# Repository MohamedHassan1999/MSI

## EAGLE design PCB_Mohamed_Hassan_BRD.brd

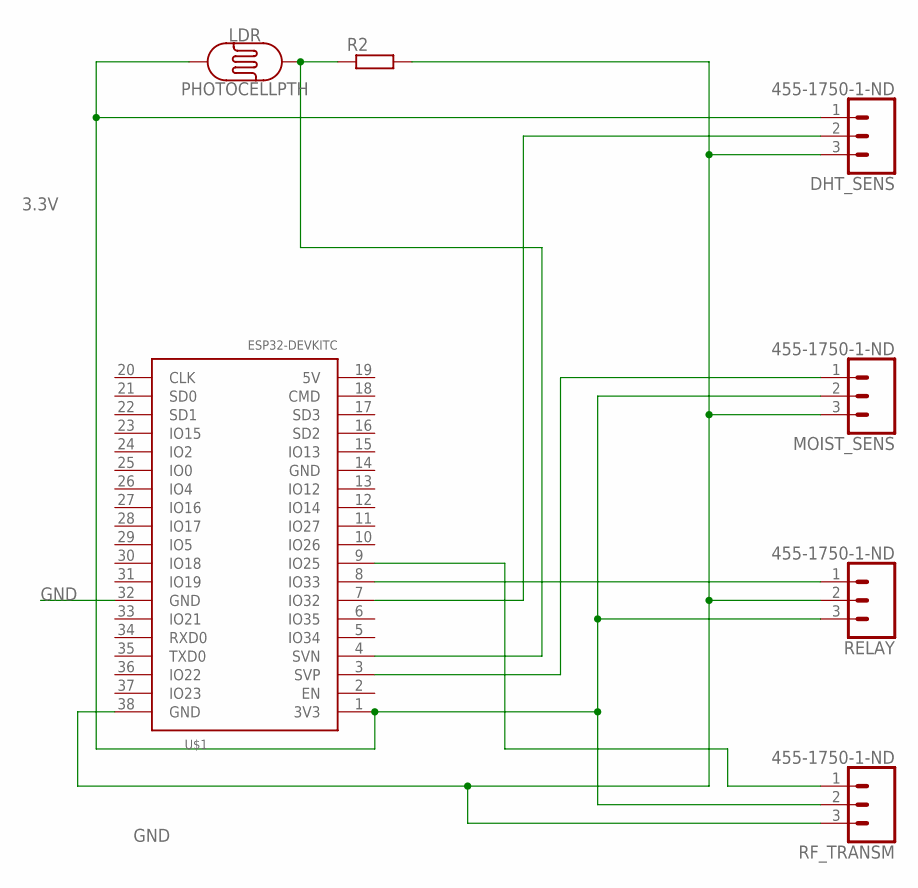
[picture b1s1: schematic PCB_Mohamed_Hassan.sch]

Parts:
DHT_SENS: 455-1750-1-ND; 1X03
LDR: PHOTOCELLPTH; PHOTOCELL
MOIST_SENS: 455-1750-1-ND; 1X03
R2: R-EU_0207/10; 0207/10
RELAY: 455-1750-1-ND; 1X03
RF_TRANSM: 455-1750-1-ND; 1X03
U$1: ESP32DEVKITC; ESP32-DEVKITC

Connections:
3.3V: DHT_SENS.1, LDR.1, MOIST_SENS.2, RELAY.3, RF_TRANSM.2, U$1.1 (3V3)
GND: DHT_SENS.3, MOIST_SENS.3, R2.2, RELAY.2, RF_TRANSM.3, U$1.32 (GND), U$1.38 (GND)
unnamed: LDR.2, R2.1, U$1.4 (SVN)
unnamed: DHT_SENS.2, U$1.7 (IO32)
unnamed: RELAY.1, U$1.8 (IO33)
unnamed: MOIST_SENS.1, U$1.3 (SVP)
unnamed: RF_TRANSM.1, U$1.9 (IO25)

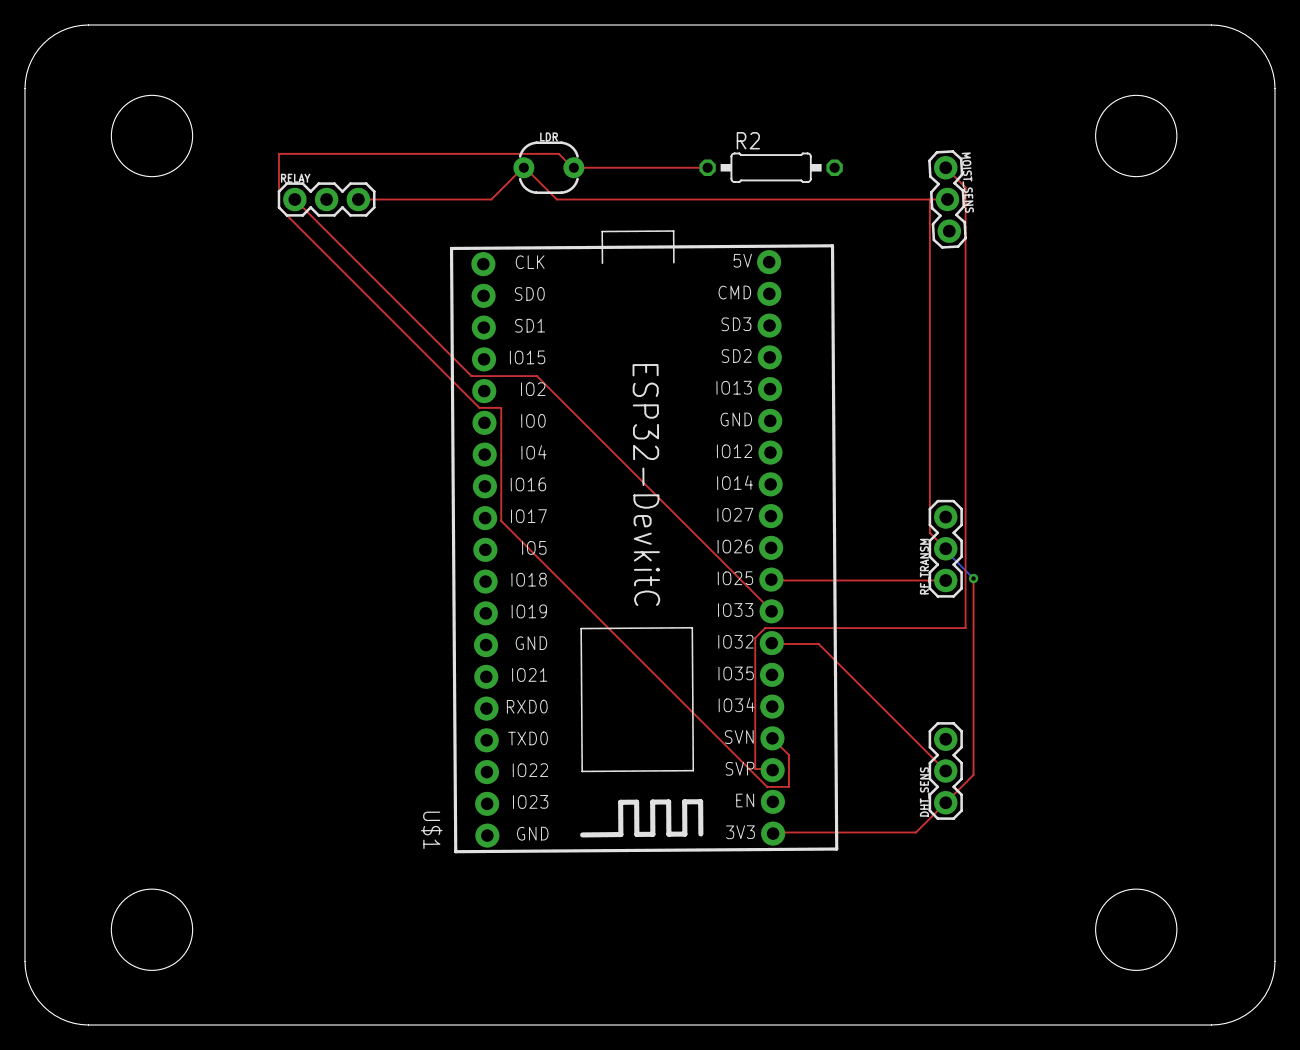
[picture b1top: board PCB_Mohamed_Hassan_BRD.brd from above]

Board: 2 copper layers, 100.0 x 80.0 mm, 7 parts (0 on the bottom side), 7 nets.

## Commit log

2021-11-03 added new files

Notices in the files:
parts and their libraries:
SparkFun-Sensors: Licensing: Creative Commons ShareAlike 4.0 International - https://creativecommons.org/licenses/by-sa/4.0
